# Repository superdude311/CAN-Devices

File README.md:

# CAN-Devices
This project serves to create 2 CAN-related PCBs for the FRC space, and I welcome everyone in the community to use these designs for their robots and customize them in whatever way they want. However, I do ask that the community refrain from selling boards made from this design, and I would prefer for teams to leave on the silkscreen markings of my design (but feel free to add your own)

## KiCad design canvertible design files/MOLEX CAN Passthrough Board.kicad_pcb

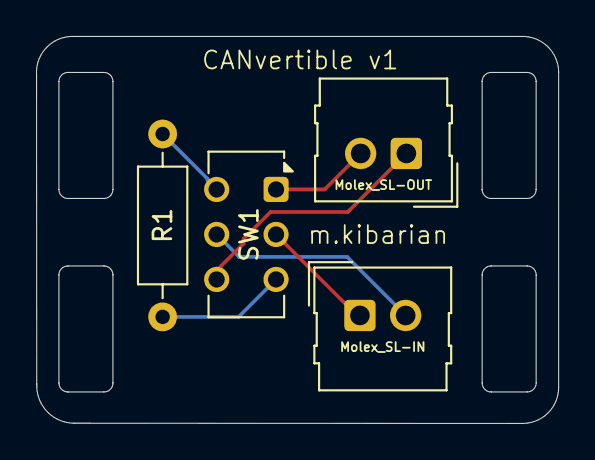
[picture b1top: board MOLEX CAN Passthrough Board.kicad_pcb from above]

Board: 2 copper layers, 29.0 x 21.5 mm, 4 parts (0 on the bottom side), 6 nets.

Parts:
Molex_SL-IN: Molex_SL_171971-0002_1x02_P2.54mm_Vertical
Molex_SL-OUT: Molex_SL_171971-0002_1x02_P2.54mm_Vertical
R1: 120ohm; R_Axial_DIN0207_L6.3mm_D2.5mm_P10.16mm_Horizontal
SW1: SW_DPDT_x2; SW_CK_JS202011CQN_DPDT_Straight

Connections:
CAN-H-IN: Molex_SL-IN.2, SW1.5 (B)
CAN-H-OUT: Molex_SL-OUT.1, SW1.4 (A)
CAN-L-IN: Molex_SL-IN.1, SW1.2 (B)
CAN-L-OUT: Molex_SL-OUT.2, SW1.1 (A)
unnamed: R1.1, SW1.3 (C)
unnamed: R1.2, SW1.6 (C)

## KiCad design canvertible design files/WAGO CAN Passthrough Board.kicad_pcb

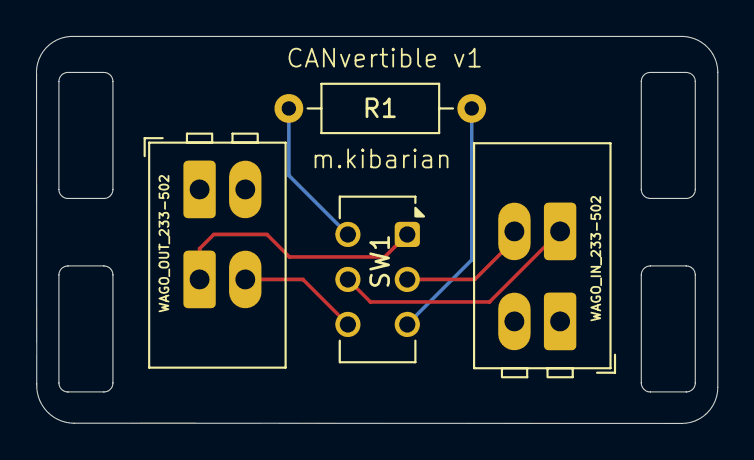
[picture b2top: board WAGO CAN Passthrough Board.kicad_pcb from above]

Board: 2 copper layers, 37.9 x 21.5 mm, 4 parts (0 on the bottom side), 6 nets.

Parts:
R1: 120ohm; R_Axial_DIN0207_L6.3mm_D2.5mm_P10.16mm_Horizontal
SW1: SW_DPDT_x2; SW_CK_JS202011CQN_DPDT_Straight
WAGO_IN_233-502: TerminalBlock_WAGO_233-502_2x02_P2.54mm
WAGO_OUT_233-502: TerminalBlock_WAGO_233-502_2x02_P2.54mm

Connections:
CAN-H-IN: SW1.5 (B), WAGO_IN_233-502.1
CAN-H-OUT: SW1.4 (A), WAGO_OUT_233-502.2
CAN-L-IN: SW1.2 (B), WAGO_IN_233-502.2
CAN-L-OUT: SW1.1 (A), WAGO_OUT_233-502.1
unnamed: R1.1, SW1.3 (C)
unnamed: R1.2, SW1.6 (C)

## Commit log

2024-11-10 CANvertible uploaded
2024-11-10 terminator uploaded
